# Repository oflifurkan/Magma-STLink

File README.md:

MAGMA STLink
============

STLink V2 design that I designed in KiCAD as a hobby for programming STM32 and STM8 microcontrollers

## What's required? 

* STM32F103C8 - with STLink V2 firmware
* 8 Mhz Crystal

* LM1117 - 5V to 3.3V LDO

* USB A Connector
* PTC Fuse
* Couple of 0805 package capacitors and resistor  

## CAD Software

* The latest KiCAD version

## Images

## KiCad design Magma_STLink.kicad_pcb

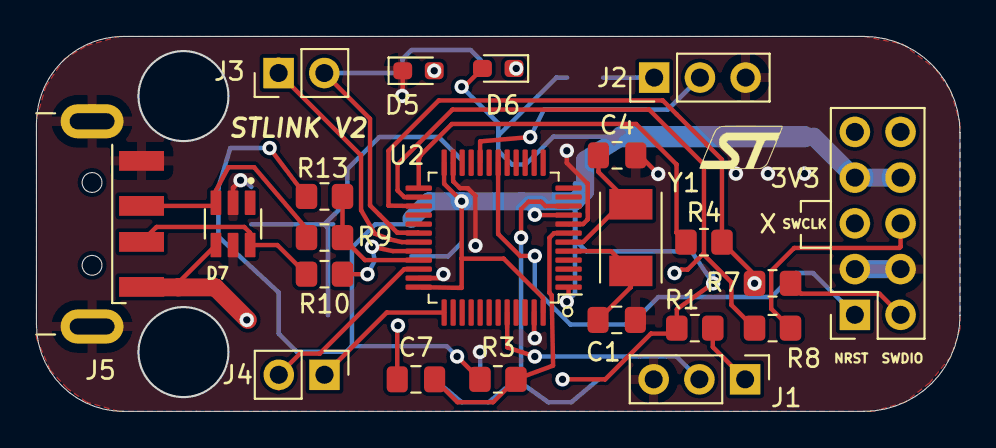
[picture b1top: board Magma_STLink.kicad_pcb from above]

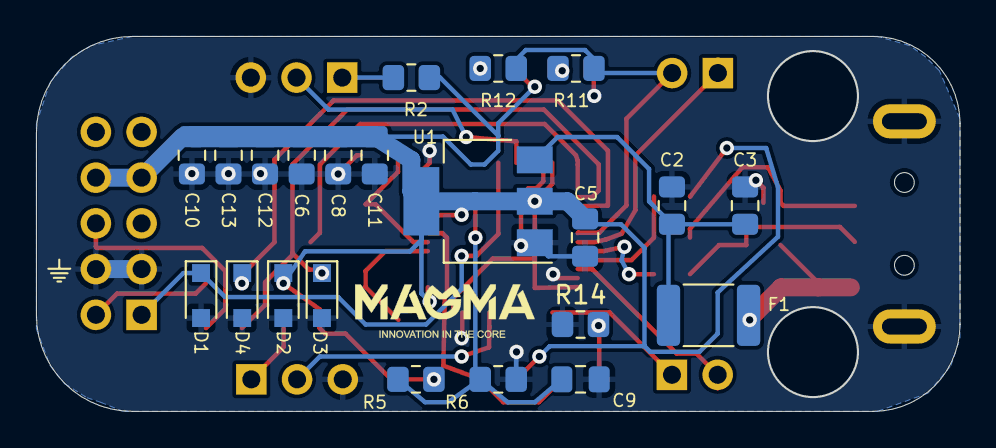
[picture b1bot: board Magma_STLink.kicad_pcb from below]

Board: 2 copper layers, 51.3 x 20.8 mm, 44 parts (22 on the bottom side), 29 nets.

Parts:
C1, C4: 18pF; C_0805_2012Metric_Pad1.18x1.45mm_HandSolder
C2, C5: 10uF; C_0805_2012Metric_Pad1.18x1.45mm_HandSolder
C3, C6, C7, C8, C9, C10, C11, C12, C13: 100nF; C_0805_2012Metric_Pad1.18x1.45mm_HandSolder
D1, D2, D3, D4: PESD3V3L1BA,115; D_SOD-323_HandSoldering
D5: RED LED; LED_0603_1608Metric_Pad1.05x0.95mm_HandSolder
D6: BLUE RED; LED_0603_1608Metric_Pad1.05x0.95mm_HandSolder
D7: ESDA6V1BC6; SOT95P280X145-6N
F1: 8V 2A; Fuse_1812_4532Metric_Pad1.30x3.40mm_HandSolder
J1, J2: Conn_01x03; PinHeader_1x03_P2.54mm_Vertical
J3, J4: Conn_01x02; PinHeader_1x02_P2.54mm_Vertical
J5: USB_A; USB_A_CNCTech_1001-011-01101_Horizontal
R1, R2: 10K; R_0805_2012Metric_Pad1.20x1.40mm_HandSolder
R3, R5, R6, R13, R14: 100K; R_0805_2012Metric_Pad1.20x1.40mm_HandSolder
R4: 220R; R_0805_2012Metric_Pad1.20x1.40mm_HandSolder
R7, R8, R9, R10: 75R; R_0805_2012Metric_Pad1.20x1.40mm_HandSolder
R11, R12: 200; R_0805_2012Metric_Pad1.20x1.40mm_HandSolder
STLINK_CONN1: STLINK CONN; PinSocket_2x05_P2.54mm_Vertical
U1: LM1117-3.3; SOT-223-3_TabPin2
U2: STM32F103C8Tx; LQFP-48_7x7mm_P0.5mm
Y1: Crystal; Crystal_SMD_TXC_7A-2Pin_5x3.2mm

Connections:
+3V3: C5.1, C6.1, C8.1, C10.1, C11.1, C12.1, C13.1, D2.1, D6.2, R1.2, R2.2, R3.2, R5.1, R13.2, STLINK_CONN1.7, STLINK_CONN1.8, U1.2, U2.1, U2.9, U2.24, U2.36, U2.48
/BOOT0: J1.2, U2.44
/BOOT1: J2.2, U2.20
/NRST: D1.1, STLINK_CONN1.1, U2.18
/OSC_IN: C1.1, U2.5, Y1.1
/OSC_OUT: C4.1, U2.6, Y1.2
/STLINK_SWCLK: D3.1, R8.1, U2.26
/STLINK_SWDIO: D4.1, R4.2, R7.1, U2.27
/SWCLK: J4.1, U2.37
/SWDIO: J4.2, U2.34
/UART_RX: J3.1, U2.31
/UART_TX: J3.2, R11.2, R12.2, U2.30
/USB_N: R10.1, U2.32
/USB_P: R9.1, R13.1, U2.33
GND: C1.2, C2.2, C3.2, C4.2, C5.2, C6.2, C8.2, C9.2, C10.2, C11.2, C12.2, C13.2, D1.2, D2.2, D3.2, D4.2, D5.1, D7.2, D7.5, J1.3, J2.3, J5.4, J5.5, R6.2, R14.1, STLINK_CONN1.3, STLINK_CONN1.4, U1.1, U2.8, U2.23, U2.35, U2.47
unnamed: C2.1, C3.1, F1.2, U1.3
unnamed: C7.1, R3.1, U2.7
unnamed: C7.2, R14.2
unnamed: C9.1, R5.2, R6.1, U2.10
unnamed: D5.2, R11.1
unnamed: D6.1, R12.1
unnamed: D7.3, J5.3, R9.2
unnamed: D7.6, J5.2, R10.2
unnamed: J1.1, R1.1
unnamed: J2.1, R2.1
unnamed: R4.1, U2.25
unnamed: R7.2, STLINK_CONN1.2
unnamed: R8.2, STLINK_CONN1.6
VBUS: D7.4, F1.1, J5.1

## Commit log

2021-09-20 Magma STLink STLink bulunamamasından dolayı Magma STLink yapılması kararlaştırıldı ve başlatıldı.
2021-09-22 STLink şematikleri değiştirildi. Konnektörlerin kararlaştırılması gerekiyor. PCB boyutu önemli. USB ESD koruması eklendi.SWDIO ve SWCLK pinlerine tekli koruma diyotu eklendi.
2021-09-22 Kütüphane eklendi.
2021-09-22 Diyot kütüphanesi eklendi.
2021-09-22 README eklendi.
2021-09-22 README yenileme
2021-09-22 README yeniden yenileme.
2021-09-22 SON AG
2021-09-22 PCB
    PCB'ye geçildi. Boyutları düzeltilerek PCB'ye devam edilecek.
2021-09-24 Kütüphane güncellemeleri
    * ESDA6V1BC6 kütüphanesi eklendi.
    * Magma logo oluşturuldu.
    * TXC 7A serisindeki kristal için Enes Ünsal'a step (3 boyutlu model) çizdirildi.
    * USB tip A plug komponentinin step dosyası eklendi.
2021-09-24 PCB tamamlandı * PCB tamamlandı ve şematikte küçük değişiklikler yapıldı. * DRC yapıldı herhangi bir hata çıkmadı.
2021-10-01 Reset'e bir direnç eklendi. Anlık resetleyebilmek için 0805 kılıfında bir direnç eklendi.
2021-10-08 Son Değişiklikler ve step
2021-10-08 son kaydedilen V1 üretime hazır.
2023-08-17 Update project to latest KiCAD version
2023-08-17 Create LICENSE
